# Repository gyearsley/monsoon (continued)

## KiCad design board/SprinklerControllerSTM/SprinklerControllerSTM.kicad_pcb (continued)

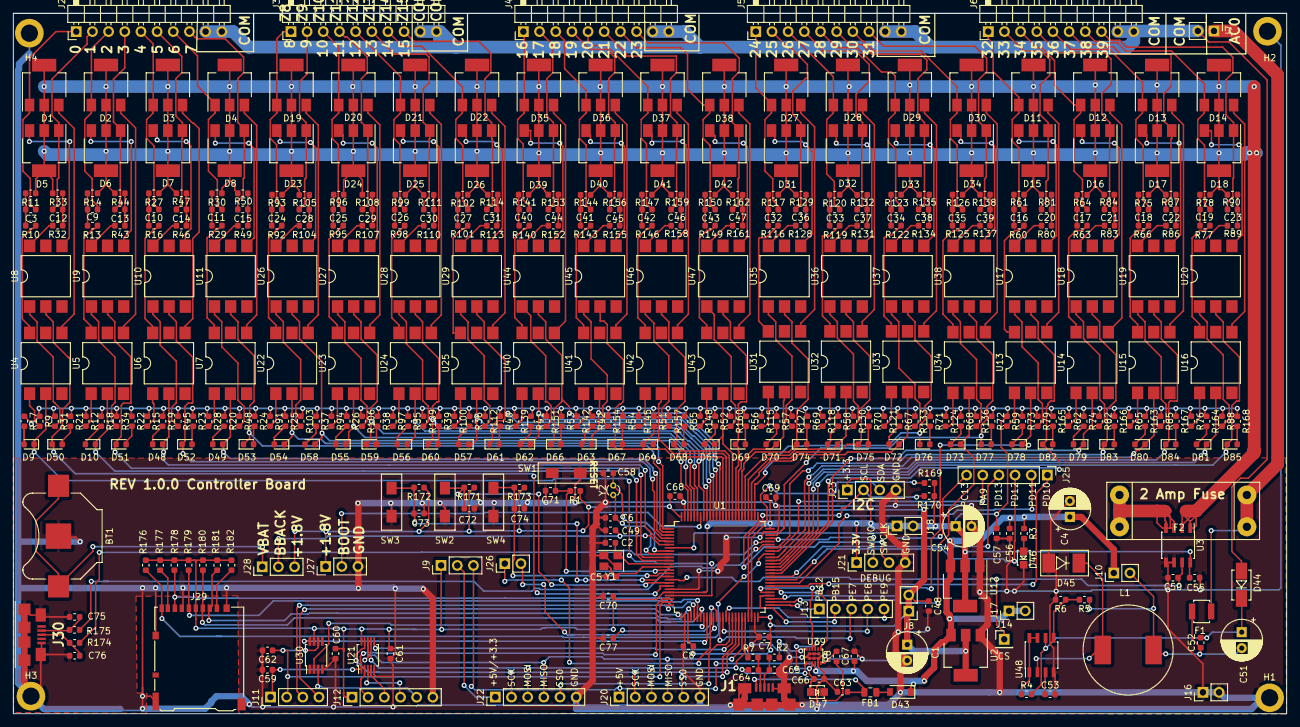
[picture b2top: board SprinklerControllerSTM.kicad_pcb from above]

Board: 2 copper layers, 200.0 x 110.0 mm, 434 parts (0 on the bottom side), 364 nets.

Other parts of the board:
BT1: Battery_Cell; BatteryHolder_Keystone_3000_1x12mm
C2, C5: 18pf; C_0603_1608Metric
C6, C58: 11pf; C_0603_1608Metric
C7, C8, C48, C49, C59, C60, C61, C62, C66, C67, C69, C70, C71, C77: 0.1uf; C_0603_1608Metric
C63: 0.01uf; C_0603_1608Metric
C64, C65, C75, C76: 47pf; C_0603_1608Metric
D43: MBR0520LT; D_SOD-123
D47: LED; led_lxt0805gw_tr
FB1: BLM21AG60; R_0805_2012Metric
J1, J30: USB_B_Micro; ZX62_AB_5PA
J21: Conn_01x04; PinHeader_1x04_P2.54mm_Vertical
J27, J28: Conn_01x03; PinHeader_1x03_P2.54mm_Vertical
J29: Micro_SD_Card_Det_Hirose_DM3AT; microSD_HC_Hirose_DM3AT-SF-PEJM5
R1: 1K; R_0603_1608Metric
R2, R7, R174, R175: 27; R_0603_1608Metric
R8: 330; R_0603_1608Metric
R176, R177, R178, R179, R180, R181, R182: 1000; R_0603_1608Metric
SW1: SW_Push; series_95C_switch_spst_pb_smd
U1: STM32F078VBTx; LQFP-100_14x14mm_P0.5mm
U21: mcp6s93; MSOP-10_3x3mm_P0.5mm
U30: MCP6G03; MSOP-8_3x3mm_P0.65mm
U39: FT234XD; FT234
Y1: 16Mhz; Crystal_SMD_3225-4Pin_3.2x2.5mm
Y2: 32Khz; Crystal_DS10_D1.0mm_L4.3mm_Vertical

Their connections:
+1V8: C7.1, C8.1, C48.1, J27.1, J28.3, R1.1, U1.28, U1.50, U1.100; also elsewhere on the board
+3V3: C60.1, C61.1, C69.1, C70.1, J21.1, J29.4, R176.2, R177.2, R178.2, R179.2, R180.2, R181.2, R182.2, U1.21, U1.75, U21.10, U30.7; also elsewhere on the board
+5V: C67.1, D43.1, U39.4; also elsewhere on the board
/ADC0: C59.1, U1.23, U21.1; also elsewhere on the board
/ADC1: C62.1, U1.24, U30.6; also elsewhere on the board
/ADC2: U1.25; also elsewhere on the board
/ADC3: U1.26; also elsewhere on the board
/CS1: U1.34, U30.8
/CurrentSense: U1.17; also elsewhere on the board
/GSEL: U1.33, U30.2
/I2C2_SCL: U1.47; also elsewhere on the board
/I2C2_SDA: U1.48; also elsewhere on the board
/PA9: U1.68; also elsewhere on the board
/PB0: U1.35; also elsewhere on the board
/PB1: U1.36; also elsewhere on the board
/PB12: U1.51; also elsewhere on the board
/PB15: U1.54; also elsewhere on the board
/PC13: U1.7; also elsewhere on the board
/PD10: U1.57; also elsewhere on the board
/PD11: U1.58; also elsewhere on the board
/PD12: U1.59; also elsewhere on the board
/PD13: U1.60; also elsewhere on the board
/PE7: U1.38; also elsewhere on the board
/PE8: U1.39; also elsewhere on the board
/PE9: U1.40; also elsewhere on the board
/RXD: U1.55, U39.10
/SE0: U1.22; also elsewhere on the board
/SE1: U1.19; also elsewhere on the board
/SE2: U1.11; also elsewhere on the board
/SE3: U1.10; also elsewhere on the board
/SE4: U1.5; also elsewhere on the board
/SE5: U1.4; also elsewhere on the board
/SE6: U1.3; also elsewhere on the board
/SE7: U1.2; also elsewhere on the board
/SE8: U1.1; also elsewhere on the board
/SE9: U1.98; also elsewhere on the board
/SE10: U1.97; also elsewhere on the board
/SE11: U1.96; also elsewhere on the board
/SE12: U1.95; also elsewhere on the board
/SE13: U1.93; also elsewhere on the board
/SE14: U1.92; also elsewhere on the board
/SE15: U1.91; also elsewhere on the board
/SE16: U1.90; also elsewhere on the board
/SE17: U1.89; also elsewhere on the board
/SE18: U1.88; also elsewhere on the board
/SE19: U1.87; also elsewhere on the board
/SE20: U1.86; also elsewhere on the board
/SE21: U1.85; also elsewhere on the board
/SE22: U1.84; also elsewhere on the board
/SE23: U1.83; also elsewhere on the board
/SE24: U1.82; also elsewhere on the board
/SE25: U1.81; also elsewhere on the board
/SE26: U1.80; also elsewhere on the board
/SE27: U1.79; also elsewhere on the board
/SE28: U1.78; also elsewhere on the board
/SE29: U1.77; also elsewhere on the board
/SE30: U1.52; also elsewhere on the board
/SE31: U1.73; also elsewhere on the board
/SE32: U1.53; also elsewhere on the board
/SE33: U1.62; also elsewhere on the board
/SE34: U1.61; also elsewhere on the board
/SE35: U1.69; also elsewhere on the board
/SE36: U1.66; also elsewhere on the board
/SE37: U1.65; also elsewhere on the board
/SE38: U1.64; also elsewhere on the board
/SE39: U1.63; also elsewhere on the board
/SPI1_MISO: U1.45, U21.8; also elsewhere on the board
/SPI1_MOSI: U1.46, U21.7; also elsewhere on the board
/SPI1_SCK: U1.44, U21.9; also elsewhere on the board
/SPI1_SS0: U1.43; also elsewhere on the board
/SPI1_SS1: U1.42, U21.6
/SPI1_SS2: U1.41; also elsewhere on the board
/SW2: U1.18; also elsewhere on the board
/SW3: U1.16; also elsewhere on the board
/SW4: U1.15; also elsewhere on the board
/TXD: U1.56, U39.7
/USBSerial/CBUS: R8.2, U39.6
/USBSerial/LED_MID: D47.1, R8.1
/USBSerial/USB+: C65.1, J1.3, R2.2
/USBSerial/USB+PR: R2.1, U39.12
/USBSerial/USB-: C64.1, J1.2, R7.2
/USBSerial/USB-PR: R7.1, U39.1
/USBSerial/VUSB: C63.2, FB1.2, J1.1
/USBSerial/ser1_3_3V: C66.1, D47.2, U39.3, U39.9
/VIN0_0: U21.2; also elsewhere on the board
/VIN0_1: U21.3; also elsewhere on the board
/VIN1: U30.3; also elsewhere on the board
/VREF: U21.4; also elsewhere on the board
/cpu_stm32/BOOT: J27.2, U1.94
/cpu_stm32/NPOR: C77.1, U1.37
/cpu_stm32/NRST: C71.1, R1.2, SW1.1, U1.14
/cpu_stm32/SD_SPI_DET: J29.9, R176.1, U1.67
/cpu_stm32/SD_SPI_MISO: J29.7, R178.1, U1.31
/cpu_stm32/SD_SPI_MOSI: J29.3, R180.1, U1.32
/cpu_stm32/SD_SPI_SCK: J29.5, R179.1, U1.30
/cpu_stm32/SD_SPI_SS0: J29.2, R181.1, U1.29
/cpu_stm32/SWCLK: J21.3, U1.76
/cpu_stm32/SWDIO: J21.2, U1.72
/cpu_stm32/USB+: C76.1, J30.3, R174.2
/cpu_stm32/USB-: C75.1, J30.2, R175.2
/cpu_stm32/USB_DM: R175.1, U1.70
/cpu_stm32/USB_DP: R174.1, U1.71
/cpu_stm32/VBAT: C49.1, J28.2, U1.6
/cpu_stm32/XTAL1: C2.1, U1.12, Y1.1
/cpu_stm32/XTAL1_32Khz: C6.1, U1.9, Y2.1
/cpu_stm32/XTAL2: C5.1, U1.13, Y1.3
/cpu_stm32/XTAL2_32Khz: C58.1, U1.8, Y2.2
GND: BT1.2, C2.2, C5.2, C6.2, C7.2, C8.2, C48.2, C49.2, C58.2, C59.2, C60.2, C61.2, C62.2, C63.1, C64.2, C65.2, C66.2, C67.2, C69.2, C70.2, C71.2, C75.2, C76.2, C77.2, J1.5, J1.6, J21.4, J27.3, J29.6, J29.11, J30.5, J30.6, SW1.2, U1.20, U1.27, U1.49, U1.74, U1.99, U21.5, U30.4, U39.5, U39.13, Y1.2, Y1.4; also elsewhere on the board
unnamed: BT1.1, J28.1
unnamed: D43.2, FB1.1
unnamed: J29.1, R182.1
unnamed: J29.8, R177.1

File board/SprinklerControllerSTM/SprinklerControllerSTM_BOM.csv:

Reference,Value,Footprint,Checked
J2;J3;J4;J5;J6,Screw_Terminal_01x10,PinHeader_1x10_P2.54mm_Horizontal,
J7,Screw_Terminal_01x02,PinHeader_1x02_P2.54mm_Vertical,
H1;H2;H3;H4,MountingHole_Pad,MountingHole_2.7mm_M2.5_ISO7380_Pad,
J20;J22;J25;J12,Conn_01x06,PinHeader_1x06_P2.54mm_Vertical,
J9;J27;J28,Conn_01x03,PinHeader_1x03_P2.54mm_Vertical,
J23;J11;J21,Conn_01x04,PinHeader_1x04_P2.54mm_Vertical,
R169;R170;R181;R180;R179;R178;R177;R182;R176,1000,R_0603_1608Metric,
J13,Conn_01x05,PinHeader_1x05_P2.54mm_Vertical,
J26;J10;J16;J17;J18;J8,Conn_01x02,PinHeader_1x02_P2.54mm_Vertical,
SW2;SW3;SW4;SW1,SW_Push,series_95C_switch_spst_pb_smd,
R171;R172;R173;R1,1K,R_0603_1608Metric,
C72;C73;C74;C3;C9;C10;C11;C12;C13;C14;C15;C66;C67;C24;C25;C26;C27;C28;C29;C30;C31;C40;C41;C42;C43;C44;C45;C46;C47;C52;C55;C56;C50;C57;C68;C32;C33;C34;C35;C36;C37;C38;C39;C16;C17;C18;C19;C20;C21;C22;C23;C60;C61;C59;C62;C7;C8;C48;C49;C69;C70;C71,0.1uf,C_0603_1608Metric,
J14,Conn_01x01,PinHeader_1x01_P2.54mm_Vertical,
U4;U5;U6;U7;U8;U9;U10;U11;U22;U23;U24;U25;U26;U27;U28;U29;U40;U41;U42;U43;U44;U45;U46;U47;U31;U32;U33;U34;U35;U36;U37;U38;U13;U14;U15;U16;U17;U18;U19;U20,MOC3012M,SMDIP-6_W9.53mm,
R10;R13;R16;R29;R32;R43;R46;R49;R92;R95;R98;R101;R104;R107;R110;R113;R140;R143;R146;R149;R152;R155;R158;R161;R116;R119;R122;R125;R128;R131;R134;R137;R60;R63;R66;R77;R80;R83;R86;R89,180,R_0603_1608Metric,
R11;R14;R27;R30;R33;R44;R47;R50;R93;R96;R99;R102;R105;R108;R111;R114;R141;R144;R147;R150;R153;R156;R159;R162;R117;R120;R123;R126;R129;R132;R135;R138;R61;R64;R75;R78;R81;R84;R87;R90,2.3K,R_0603_1608Metric,
R9;R17;R12;R18;R15;R19;R28;R20;R31;R21;R34;R22;R45;R23;R48;R24;R91;R25;R94;R26;R97;R35;R100;R36;R103;R37;R106;R38;R109;R39;R112;R40;R139;R41;R142;R42;R145;R51;R148;R52;R151;R53;R154;R54;R157;R55;R160;R56;R115;R57;R118;R58;R121;R67;R124;R68;R127;R69;R130;R70;R133;R71;R136;R72;R59;R73;R62;R74;R65;R163;R76;R164;R79;R165;R82;R166;R85;R167;R88;R168,510,R_0603_1608Metric,
D1;D2;D3;D4;D5;D6;D7;D8;D19;D20;D21;D22;D23;D24;D25;D26;D35;D36;D37;D38;D39;D40;D41;D42;D27;D28;D29;D30;D31;D32;D33;D34;D11;D12;D13;D14;D15;D16;D17;D18,Z0103MN,SOT-223,
D9;D10;D48;D49;D50;D51;D52;D53;D54;D55;D56;D57;D58;D59;D60;D61;D62;D63;D64;D65;D66;D67;D68;D69;D70;D71;D72;D73;D74;D75;D76;D77;D78;D79;D80;D81;D82;D83;D84;D85,LED_STAT,LED_0603_1608Metric,
J1;J30,USB_B_Micro,ZX62_AB_5PA,
D43,MBR0520LT,D_SOD-123,
U39,FT234XD,FT234,
R8;R3,330,R_0603_1608Metric,
D47;D46,LED,led_lxt0805gw_tr,
C64;C65;C75;C76,47pf,C_0603_1608Metric,
R7;R2;R175;R174,27,R_0603_1608Metric,
FB1,BLM21AG60,R_0805_2012Metric,
C63,0.01uf,C_0603_1608Metric,
U48,MC34063AD,SOIC-8_3.9x4.9mm_P1.27mm,
C53,470pf,C_0603_1608Metric,
C51;C1,100uf,CP_Radial_D6.3mm_P2.50mm,
R4,0.2,R_0603_1608Metric,
R5,3600,R_0603_1608Metric,
R6,1200,R_0603_1608Metric,
D44,RS1G,DO-214AC,
L1,220uh,Taiyo_inductor_10050,
D45,BYV10-40a,Schottky_diode_TMBYV_10_40,
F2,Fuse,OG_Clip_5x20,
F1,Fuse,Bourns_resettable_fuse,
C4;C54,470uf,CP_Radial_D6.3mm_P2.50mm,
U3,ACS723xLCTR-05AB,SOIC-8_3.9x4.9mm_P1.27mm,
U12,LT1117-3.3,SOT-223-3_TabPin2,
U2,NCP1117-1.8_SOT223,SOT-223-3_TabPin2,
U21,mcp6s93,MSOP-10_3x3mm_P0.5mm,
U30,MCP6G03,MSOP-8_3x3mm_P0.65mm,
C2;C5,18pf,C_0603_1608Metric,
Y1,16Mhz,Crystal_SMD_3225-4Pin_3.2x2.5mm,
U1,STM32F078VBTx,LQFP-100_14x14mm_P0.5mm,
C6;C58,11pf,C_0603_1608Metric,
Y2,32Khz,Crystal_DS10_D1.0mm_L4.3mm_Vertical,
BT1,Battery_Cell,BatteryHolder_Keystone_3000_1x12mm,
J29,Micro_SD_Card_Det_Hirose_DM3AT,microSD_HC_Hirose_DM3AT-SF-PEJM5,

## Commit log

2019-01-05 added files
